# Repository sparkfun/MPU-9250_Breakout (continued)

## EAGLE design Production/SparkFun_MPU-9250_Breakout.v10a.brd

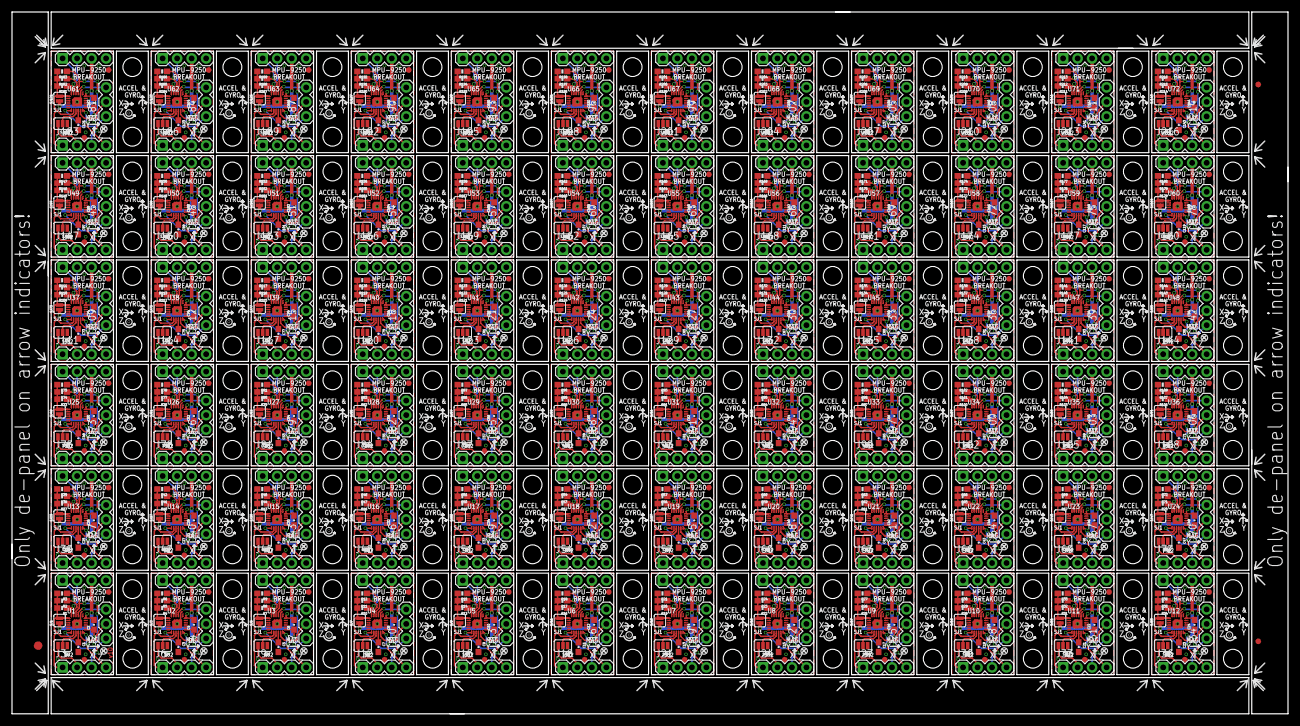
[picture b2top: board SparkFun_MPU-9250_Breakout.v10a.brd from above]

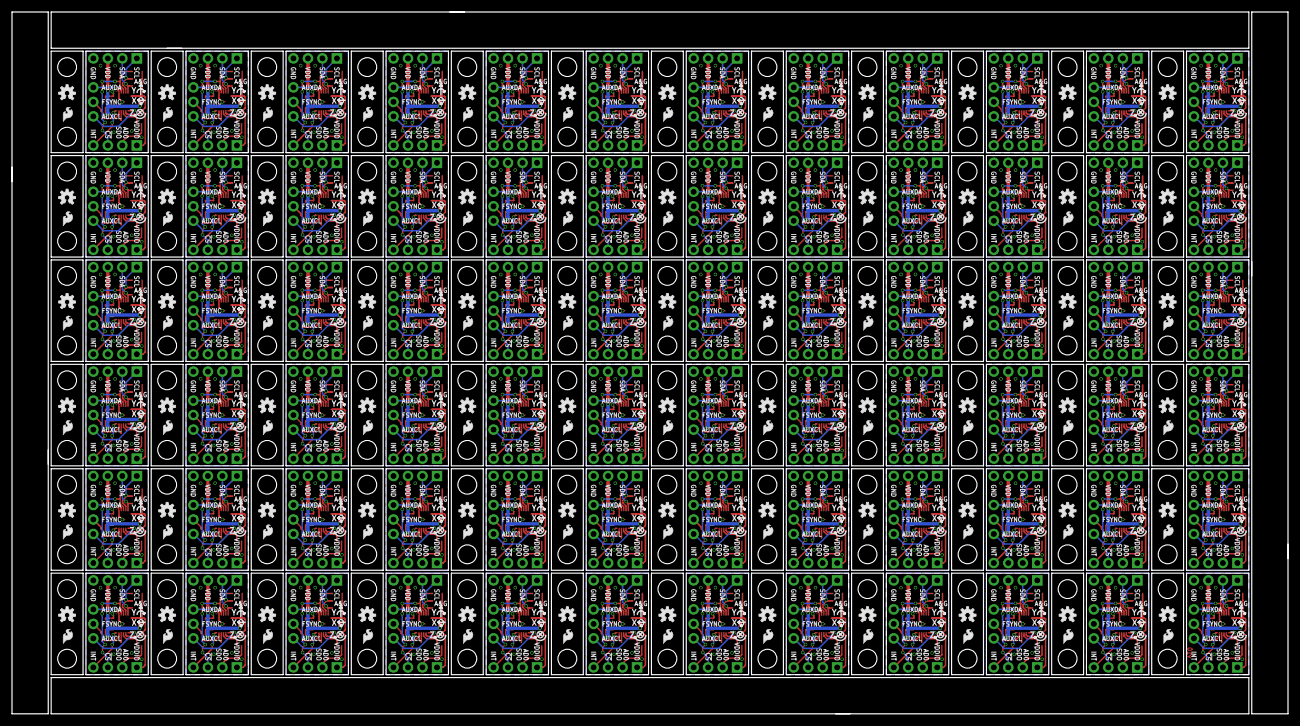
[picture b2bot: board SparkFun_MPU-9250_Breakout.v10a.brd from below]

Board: 2 copper layers, 223.5 x 122.9 mm, 1227 parts (144 on the bottom side), 936 nets.

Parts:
C1, C2, C3, C4, C5, C6, C7, C8, C9, C10, C11, C12, C13, C14, C15, C16, C17, C18, C19, C20, C21, C22, C23, C24, C25, C26, C27, C28, C29, C30, C31, C32, C33, C34, C35, C36, C37, C38, C39, C40, C41, C42, C43, C44, C45, C46, C47, C48, C49, C50, C51, C52, C53, C54, C55, C56, C57, C58, C59, C60, C61, C62, C63, C64, C65, C66, C67, C68, C69, C70, C71, C72, C73, C74, C75, C76, C77, C78, C79, C80, C81, C82, C83, C84, C85, C86, C87, C88, C89, C90, C91, C92, C93, C94, C95, C96, C97, C98, C99, C100, C101, C102, C103, C104, C105, C106, C107, C108, C109, C110, C111, C112, C113, C114, C115, C116, C117, C118, C119, C120, C121, C122, C123, C124, C125, C126, C127, C128, C129, C130, C131, C132, C133, C134, C135, C136, C137, C138, C139, C140, C141, C142, C143, C144: 0.1uF; 0603-CAP
E$1: FIDUCIAL-1.5X3
E$5, E$6: FIDUCIAL-1X2
FID1, FID2, FID3, FID4, FID5, FID6, FID7, FID8, FID9, FID10, FID11, FID12, FID13, FID14, FID15, FID16, FID17, FID18, FID19, FID20, FID21, FID22, FID23, FID24, FID25, FID26, FID27, FID28, FID29, FID30, FID31, FID32, FID33, FID34, FID35, FID36, FID37, FID38, FID39, FID40, FID41, FID42, FID43, FID44, FID45, FID46, FID47, FID48, FID49, FID50, FID51, FID52, FID53, FID54, FID55, FID56, FID57, FID58, FID59, FID60, FID61, FID62, FID63, FID64, FID65, FID66, FID67, FID68, FID69, FID70, FID71, FID72, FID73, FID74, FID75, FID76, FID77, FID78, FID79, FID80, FID81, FID82, FID83, FID84, FID85, FID86, FID87, FID88, FID89, FID90, FID91, FID92, FID93, FID94, FID95, FID96, FID97, FID98, FID99, FID100, FID101, FID102, FID103, FID104, FID105, FID106, FID107, FID108, FID109, FID110, FID111, FID112, FID113, FID114, FID115, FID116, FID117, FID118, FID119, FID120, FID121, FID122, FID123, FID124, FID125, FID126, FID127, FID128, FID129, FID130, FID131, FID132, FID133, FID134, FID135, FID136, FID137, FID138, FID139, FID140, FID141, FID142, FID143, FID144: FIDUCIAL1X2; FIDUCIAL-1X2
J1, J3, J5, J6, J8, J9, J11, J12, J14, J15, J17, J18, J20, J21, J23, J24, J26, J27, J29, J30, J32, J33, J35, J36, J38, J39, J41, J42, J44, J45, J47, J48, J50, J51, J53, J54, J56, J57, J59, J60, J62, J63, J65, J66, J68, J69, J71, J72, J74, J75, J77, J78, J80, J81, J83, J84, J86, J87, J89, J90, J92, J93, J95, J96, J98, J99, J101, J102, J104, J105, J107, J108, J110, J111, J113, J114, J116, J117, J119, J120, J122, J123, J125, J126, J128, J129, J131, J132, J134, J135, J137, J138, J140, J141, J143, J144, J146, J147, J149, J150, J152, J153, J155, J156, J158, J159, J161, J162, J164, J165, J167, J168, J170, J171, J173, J174, J176, J177, J179, J180, J182, J183, J185, J186, J188, J189, J191, J192, J194, J195, J197, J198, J200, J201, J203, J204, J206, J207, J209, J210, J212, J213, J215, J216: 1X04
J2, J4, J7, J10, J13, J16, J19, J22, J25, J28, J31, J34, J37, J40, J43, J46, J49, J52, J55, J58, J61, J64, J67, J70, J73, J76, J79, J82, J85, J88, J91, J94, J97, J100, J103, J106, J109, J112, J115, J118, J121, J124, J127, J130, J133, J136, J139, J142, J145, J148, J151, J154, J157, J160, J163, J166, J169, J172, J175, J178, J181, J184, J187, J190, J193, J196, J199, J202, J205, J208, J211, J214: 1X03
LOGO1, LOGO3, LOGO5, LOGO7, LOGO9, LOGO11, LOGO13, LOGO15, LOGO17, LOGO19, LOGO21, LOGO23, LOGO25, LOGO27, LOGO29, LOGO31, LOGO33, LOGO35, LOGO37, LOGO39, LOGO41, LOGO43, LOGO45, LOGO47, LOGO49, LOGO51, LOGO53, LOGO55, LOGO57, LOGO59, LOGO61, LOGO63, LOGO65, LOGO67, LOGO69, LOGO71, LOGO73, LOGO75, LOGO77, LOGO79, LOGO81, LOGO83, LOGO85, LOGO87, LOGO89, LOGO91, LOGO93, LOGO95, LOGO97, LOGO99, LOGO101, LOGO103, LOGO105, LOGO107, LOGO109, LOGO111, LOGO113, LOGO115, LOGO117, LOGO119, LOGO121, LOGO123, LOGO125, LOGO127, LOGO129, LOGO131, LOGO133, LOGO135, LOGO137, LOGO139, LOGO141, LOGO143: SFE_LOGO_FLAME.1_INCH; SFE_LOGO_FLAME_.1
LOGO2, LOGO4, LOGO6, LOGO8, LOGO10, LOGO12, LOGO14, LOGO16, LOGO18, LOGO20, LOGO22, LOGO24, LOGO26, LOGO28, LOGO30, LOGO32, LOGO34, LOGO36, LOGO38, LOGO40, LOGO42, LOGO44, LOGO46, LOGO48, LOGO50, LOGO52, LOGO54, LOGO56, LOGO58, LOGO60, LOGO62, LOGO64, LOGO66, LOGO68, LOGO70, LOGO72, LOGO74, LOGO76, LOGO78, LOGO80, LOGO82, LOGO84, LOGO86, LOGO88, LOGO90, LOGO92, LOGO94, LOGO96, LOGO98, LOGO100, LOGO102, LOGO104, LOGO106, LOGO108, LOGO110, LOGO112, LOGO114, LOGO116, LOGO118, LOGO120, LOGO122, LOGO124, LOGO126, LOGO128, LOGO130, LOGO132, LOGO134, LOGO136, LOGO138, LOGO140, LOGO142, LOGO144: OSHW-LOGOS; OSHW-LOGO-S
R1, R2, R3, R4, R5, R6, R7, R8, R9, R10, R11, R12, R13, R14, R15, R16, R17, R18, R19, R20, R21, R22, R23, R24, R25, R26, R27, R28, R29, R30, R31, R32, R33, R34, R35, R36, R37, R38, R39, R40, R41, R42, R43, R44, R45, R46, R47, R48, R49, R50, R51, R52, R53, R54, R55, R56, R57, R58, R59, R60, R61, R62, R63, R64, R65, R66, R67, R68, R69, R70, R71, R72, R73, R74, R75, R76, R77, R78, R79, R80, R81, R82, R83, R84, R85, R86, R87, R88, R89, R90, R91, R92, R93, R94, R95, R96, R97, R98, R99, R100, R101, R102, R103, R104, R105, R106, R107, R108, R109, R110, R111, R112, R113, R114, R115, R116, R117, R118, R119, R120, R121, R122, R123, R124, R125, R126, R127, R128, R129, R130, R131, R132, R133, R134, R135, R136, R137, R138, R139, R140, R141, R142, R143, R144, R145, R146, R147, R148, R149, R150, R151, R152, R153, R154, R155, R156, R157, R158, R159, R160, R161, R162, R163, R164, R165, R166, R167, R168, R169, R170, R171, R172, R173, R174, R175, R176, R177, R178, R179, R180, R181, R182, R183, R184, R185, R186, R187, R188, R189, R190, R191, R192, R193, R194, R195, R196, R197, R198, R199, R200, R201, R202, R203, R204, R205, R206, R207, R208, R209, R210, R211, R212, R213, R214, R215, R216: 10K; 0603-RES
SJ1, SJ3, SJ5, SJ7, SJ9, SJ11, SJ13, SJ15, SJ17, SJ19, SJ21, SJ23, SJ25, SJ27, SJ29, SJ31, SJ33, SJ35, SJ37, SJ39, SJ41, SJ43, SJ45, SJ47, SJ49, SJ51, SJ53, SJ55, SJ57, SJ59, SJ61, SJ63, SJ65, SJ67, SJ69, SJ71, SJ73, SJ75, SJ77, SJ79, SJ81, SJ83, SJ85, SJ87, SJ89, SJ91, SJ93, SJ95, SJ97, SJ99, SJ101, SJ103, SJ105, SJ107, SJ109, SJ111, SJ113, SJ115, SJ117, SJ119, SJ121, SJ123, SJ125, SJ127, SJ129, SJ131, SJ133, SJ135, SJ137, SJ139, SJ141, SJ143: JUMPER-PAD-2-NC_BY_PASTEFULL-BOX-SILK; PAD-JUMPER-2-NC_BY_PASTE_YES_SILK_FULL_BOX
SJ2, SJ4, SJ6, SJ8, SJ10, SJ12, SJ14, SJ16, SJ18, SJ20, SJ22, SJ24, SJ26, SJ28, SJ30, SJ32, SJ34, SJ36, SJ38, SJ40, SJ42, SJ44, SJ46, SJ48, SJ50, SJ52, SJ54, SJ56, SJ58, SJ60, SJ62, SJ64, SJ66, SJ68, SJ70, SJ72, SJ74, SJ76, SJ78, SJ80, SJ82, SJ84, SJ86, SJ88, SJ90, SJ92, SJ94, SJ96, SJ98, SJ100, SJ102, SJ104, SJ106, SJ108, SJ110, SJ112, SJ114, SJ116, SJ118, SJ120, SJ122, SJ124, SJ126, SJ128, SJ130, SJ132, SJ134, SJ136, SJ138, SJ140, SJ142, SJ144: JUMPER_PAD-3-1&2_NC_BY_PASTE; PAD-HUMPER-3-1&2_NC_BY_PASTE_YES_SILK_FULL_BOX
STANDOFF1, STANDOFF2, STANDOFF3, STANDOFF4, STANDOFF5, STANDOFF6, STANDOFF7, STANDOFF8, STANDOFF9, STANDOFF10, STANDOFF11, STANDOFF12, STANDOFF13, STANDOFF14, STANDOFF15, STANDOFF16, STANDOFF17, STANDOFF18, STANDOFF19, STANDOFF20, STANDOFF21, STANDOFF22, STANDOFF23, STANDOFF24, STANDOFF25, STANDOFF26, STANDOFF27, STANDOFF28, STANDOFF29, STANDOFF30, STANDOFF31, STANDOFF32, STANDOFF33, STANDOFF34, STANDOFF35, STANDOFF36, STANDOFF37, STANDOFF38, STANDOFF39, STANDOFF40, STANDOFF41, STANDOFF42, STANDOFF43, STANDOFF44, STANDOFF45, STANDOFF46, STANDOFF47, STANDOFF48, STANDOFF49, STANDOFF50, STANDOFF51, STANDOFF52, STANDOFF53, STANDOFF54, STANDOFF55, STANDOFF56, STANDOFF57, STANDOFF58, STANDOFF59, STANDOFF60, STANDOFF61, STANDOFF62, STANDOFF63, STANDOFF64, STANDOFF65, STANDOFF66, STANDOFF67, STANDOFF68, STANDOFF69, STANDOFF70, STANDOFF71, STANDOFF72, STANDOFF73, STANDOFF74, STANDOFF75, STANDOFF76, STANDOFF77, STANDOFF78, STANDOFF79, STANDOFF80, STANDOFF81, STANDOFF82, STANDOFF83, STANDOFF84, STANDOFF85, STANDOFF86, STANDOFF87, STANDOFF88, STANDOFF89, STANDOFF90, STANDOFF91, STANDOFF92, STANDOFF93, STANDOFF94, STANDOFF95, STANDOFF96, STANDOFF97, STANDOFF98, STANDOFF99, STANDOFF100, STANDOFF101, STANDOFF102, STANDOFF103, STANDOFF104, STANDOFF105, STANDOFF106, STANDOFF107, STANDOFF108, STANDOFF109, STANDOFF110, STANDOFF111, STANDOFF112, STANDOFF113, STANDOFF114, STANDOFF115, STANDOFF116, STANDOFF117, STANDOFF118, STANDOFF119, STANDOFF120, STANDOFF121, STANDOFF122, STANDOFF123, STANDOFF124, STANDOFF125, STANDOFF126, STANDOFF127, STANDOFF128, STANDOFF129, STANDOFF130, STANDOFF131, STANDOFF132, STANDOFF133, STANDOFF134, STANDOFF135, STANDOFF136, STANDOFF137, STANDOFF138, STANDOFF139, STANDOFF140, STANDOFF141, STANDOFF142, STANDOFF143, STANDOFF144: STAND-OFF
U1, U2, U3, U4, U5, U6, U7, U8, U9, U10, U11, U12, U13, U14, U15, U16, U17, U18, U19, U20, U21, U22, U23, U24, U25, U26, U27, U28, U29, U30, U31, U32, U33, U34, U35, U36, U37, U38, U39, U40, U41, U42, U43, U44, U45, U46, U47, U48, U49, U50, U51, U52, U53, U54, U55, U56, U57, U58, U59, U60, U61, U62, U63, U64, U65, U66, U67, U68, U69, U70, U71, U72: MPU-9250; QFN24_PAD

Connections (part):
!CS: J3.3, R3.1, U1.22
!CS1: J6.3, R6.1, U2.22
!CS2: J9.3, R9.1, U3.22
!CS3: J12.3, R12.1, U4.22
!CS4: J15.3, R15.1, U5.22
!CS5: J18.3, R18.1, U6.22
!CS6: J21.3, R21.1, U7.22
!CS7: J24.3, R24.1, U8.22
!CS8: J27.3, R27.1, U9.22
!CS9: J30.3, R30.1, U10.22
!CS10: J33.3, R33.1, U11.22
!CS11: J36.3, R36.1, U12.22
!CS12: J39.3, R39.1, U13.22
!CS13: J42.3, R42.1, U14.22
!CS14: J45.3, R45.1, U15.22
!CS15: J48.3, R48.1, U16.22
!CS16: J51.3, R51.1, U17.22
!CS17: J54.3, R54.1, U18.22
!CS18: J57.3, R57.1, U19.22
!CS19: J60.3, R60.1, U20.22
!CS20: J63.3, R63.1, U21.22
!CS21: J66.3, R66.1, U22.22
!CS22: J69.3, R69.1, U23.22
!CS23: J72.3, R72.1, U24.22
!CS24: J75.3, R75.1, U25.22
!CS25: J78.3, R78.1, U26.22
!CS26: J81.3, R81.1, U27.22
!CS27: J84.3, R84.1, U28.22
!CS28: J87.3, R87.1, U29.22
!CS29: J90.3, R90.1, U30.22
!CS30: J93.3, R93.1, U31.22
!CS31: J96.3, R96.1, U32.22
!CS32: J99.3, R99.1, U33.22
!CS33: J102.3, R102.1, U34.22
!CS34: J105.3, R105.1, U35.22
!CS35: J108.3, R108.1, U36.22
!CS36: J111.3, R111.1, U37.22
!CS37: J114.3, R114.1, U38.22
!CS38: J117.3, R117.1, U39.22
!CS39: J120.3, R120.1, U40.22
!CS40: J123.3, R123.1, U41.22
!CS41: J126.3, R126.1, U42.22
!CS42: J129.3, R129.1, U43.22
!CS43: J132.3, R132.1, U44.22
!CS44: J135.3, R135.1, U45.22
!CS45: J138.3, R138.1, U46.22
!CS46: J141.3, R141.1, U47.22
!CS47: J144.3, R144.1, U48.22
!CS48: J147.3, R147.1, U49.22
!CS49: J150.3, R150.1, U50.22
!CS50: J153.3, R153.1, U51.22
!CS51: J156.3, R156.1, U52.22
!CS52: J159.3, R159.1, U53.22
!CS53: J162.3, R162.1, U54.22
!CS54: J165.3, R165.1, U55.22
!CS55: J168.3, R168.1, U56.22
!CS56: J171.3, R171.1, U57.22
!CS57: J174.3, R174.1, U58.22
!CS58: J177.3, R177.1, U59.22
!CS59: J180.3, R180.1, U60.22
!CS60: J183.3, R183.1, U61.22
!CS61: J186.3, R186.1, U62.22
!CS62: J189.3, R189.1, U63.22
!CS63: J192.3, R192.1, U64.22
!CS64: J195.3, R195.1, U65.22
!CS65: J198.3, R198.1, U66.22
!CS66: J201.3, R201.1, U67.22
!CS67: J204.3, R204.1, U68.22
!CS68: J207.3, R207.1, U69.22
!CS69: J210.3, R210.1, U70.22
!CS70: J213.3, R213.1, U71.22
!CS71: J216.3, R216.1, U72.22
AD0/SDO: J3.2, SJ2.3
AD0/SDO1: J6.2, SJ4.3
AD0/SDO2: J9.2, SJ6.3
AD0/SDO3: J12.2, SJ8.3
AD0/SDO4: J15.2, SJ10.3
AD0/SDO5: J18.2, SJ12.3
AD0/SDO6: J21.2, SJ14.3
AD0/SDO7: J24.2, SJ16.3
AD0/SDO8: J27.2, SJ18.3
AD0/SDO9: J30.2, SJ20.3
AD0/SDO10: J33.2, SJ22.3
AD0/SDO11: J36.2, SJ24.3
AD0/SDO12: J39.2, SJ26.3
AD0/SDO13: J42.2, SJ28.3
AD0/SDO14: J45.2, SJ30.3
AD0/SDO15: J48.2, SJ32.3
AD0/SDO16: J51.2, SJ34.3
AD0/SDO17: J54.2, SJ36.3
AD0/SDO18: J57.2, SJ38.3
AD0/SDO19: J60.2, SJ40.3
AD0/SDO20: J63.2, SJ42.3
AD0/SDO21: J66.2, SJ44.3
AD0/SDO22: J69.2, SJ46.3
AD0/SDO23: J72.2, SJ48.3
AD0/SDO24: J75.2, SJ50.3
AD0/SDO25: J78.2, SJ52.3
AD0/SDO26: J81.2, SJ54.3
AD0/SDO27: J84.2, SJ56.3
AD0/SDO28: J87.2, SJ58.3
AD0/SDO29: J90.2, SJ60.3
AD0/SDO30: J93.2, SJ62.3
AD0/SDO31: J96.2, SJ64.3
AD0/SDO32: J99.2, SJ66.3
AD0/SDO33: J102.2, SJ68.3
AD0/SDO34: J105.2, SJ70.3
AD0/SDO35: J108.2, SJ72.3
AD0/SDO36: J111.2, SJ74.3
AD0/SDO37: J114.2, SJ76.3
AD0/SDO38: J117.2, SJ78.3
AD0/SDO39: J120.2, SJ80.3
AD0/SDO40: J123.2, SJ82.3
AD0/SDO41: J126.2, SJ84.3
AD0/SDO42: J129.2, SJ86.3
AD0/SDO43: J132.2, SJ88.3
AD0/SDO44: J135.2, SJ90.3
AD0/SDO45: J138.2, SJ92.3
AD0/SDO46: J141.2, SJ94.3
AD0/SDO47: J144.2, SJ96.3
AD0/SDO48: J147.2, SJ98.3
AD0/SDO49: J150.2, SJ100.3
AD0/SDO50: J153.2, SJ102.3
AD0/SDO51: J156.2, SJ104.3
AD0/SDO52: J159.2, SJ106.3
AD0/SDO53: J162.2, SJ108.3
AD0/SDO54: J165.2, SJ110.3
AD0/SDO55: J168.2, SJ112.3
AD0/SDO56: J171.2, SJ114.3
AD0/SDO57: J174.2, SJ116.3
AD0/SDO58: J177.2, SJ118.3
AD0/SDO59: J180.2, SJ120.3
AD0/SDO60: J183.2, SJ122.3
AD0/SDO61: J186.2, SJ124.3
AD0/SDO62: J189.2, SJ126.3
AD0/SDO63: J192.2, SJ128.3
AD0/SDO64: J195.2, SJ130.3
AD0/SDO65: J198.2, SJ132.3
AD0/SDO66: J201.2, SJ134.3
AD0/SDO67: J204.2, SJ136.3
AD0/SDO68: J207.2, SJ138.3
AD0/SDO69: J210.2, SJ140.3
AD0/SDO70: J213.2, SJ142.3
AD0/SDO71: J216.2, SJ144.3
ADSD_STUB: SJ2.2, U1.9
ADSD_STUB1: SJ4.2, U2.9
ADSD_STUB2: SJ6.2, U3.9
ADSD_STUB3: SJ8.2, U4.9
ADSD_STUB4: SJ10.2, U5.9
ADSD_STUB5: SJ12.2, U6.9
ADSD_STUB6: SJ14.2, U7.9
ADSD_STUB7: SJ16.2, U8.9
ADSD_STUB8: SJ18.2, U9.9
ADSD_STUB9: SJ20.2, U10.9
ADSD_STUB10: SJ22.2, U11.9
ADSD_STUB11: SJ24.2, U12.9
ADSD_STUB12: SJ26.2, U13.9
ADSD_STUB13: SJ28.2, U14.9
ADSD_STUB14: SJ30.2, U15.9
ADSD_STUB15: SJ32.2, U16.9
ADSD_STUB16: SJ34.2, U17.9
ADSD_STUB17: SJ36.2, U18.9
ADSD_STUB18: SJ38.2, U19.9
ADSD_STUB19: SJ40.2, U20.9
ADSD_STUB20: SJ42.2, U21.9
ADSD_STUB21: SJ44.2, U22.9
ADSD_STUB22: SJ46.2, U23.9
ADSD_STUB23: SJ48.2, U24.9
ADSD_STUB24: SJ50.2, U25.9
ADSD_STUB25: SJ52.2, U26.9
ADSD_STUB26: SJ54.2, U27.9
ADSD_STUB27: SJ56.2, U28.9
ADSD_STUB28: SJ58.2, U29.9
ADSD_STUB29: SJ60.2, U30.9
ADSD_STUB30: SJ62.2, U31.9
ADSD_STUB31: SJ64.2, U32.9
ADSD_STUB32: SJ66.2, U33.9
ADSD_STUB33: SJ68.2, U34.9
ADSD_STUB34: SJ70.2, U35.9
ADSD_STUB35: SJ72.2, U36.9
ADSD_STUB36: SJ74.2, U37.9
ADSD_STUB37: SJ76.2, U38.9
ADSD_STUB38: SJ78.2, U39.9
ADSD_STUB39: SJ80.2, U40.9
ADSD_STUB40: SJ82.2, U41.9
ADSD_STUB41: SJ84.2, U42.9
ADSD_STUB42: SJ86.2, U43.9
ADSD_STUB43: SJ88.2, U44.9
ADSD_STUB44: SJ90.2, U45.9
ADSD_STUB45: SJ92.2, U46.9
ADSD_STUB46: SJ94.2, U47.9
ADSD_STUB47: SJ96.2, U48.9
ADSD_STUB48: SJ98.2, U49.9
ADSD_STUB49: SJ100.2, U50.9
ADSD_STUB50: SJ102.2, U51.9
ADSD_STUB51: SJ104.2, U52.9
ADSD_STUB52: SJ106.2, U53.9
ADSD_STUB53: SJ108.2, U54.9
ADSD_STUB54: SJ110.2, U55.9
ADSD_STUB55: SJ112.2, U56.9
ADSD_STUB56: SJ114.2, U57.9
ADSD_STUB57: SJ116.2, U58.9
ADSD_STUB58: SJ118.2, U59.9
ADSD_STUB59: SJ120.2, U60.9
ADSD_STUB60: SJ122.2, U61.9
ADSD_STUB61: SJ124.2, U62.9
ADSD_STUB62: SJ126.2, U63.9
ADSD_STUB63: SJ128.2, U64.9
ADSD_STUB64: SJ130.2, U65.9
ADSD_STUB65: SJ132.2, U66.9
ADSD_STUB66: SJ134.2, U67.9
ADSD_STUB67: SJ136.2, U68.9
ADSD_STUB68: SJ138.2, U69.9
ADSD_STUB69: SJ140.2, U70.9
ADSD_STUB70: SJ142.2, U71.9
ADSD_STUB71: SJ144.2, U72.9
AUX_CL: J2.1, U1.7
AUX_CL1: J4.1, U2.7
AUX_CL2: J7.1, U3.7
AUX_CL3: J10.1, U4.7
AUX_CL4: J13.1, U5.7
AUX_CL5: J16.1, U6.7
AUX_CL6: J19.1, U7.7
AUX_CL7: J22.1, U8.7
AUX_CL8: J25.1, U9.7
AUX_CL9: J28.1, U10.7
AUX_CL10: J31.1, U11.7
AUX_CL11: J34.1, U12.7
AUX_CL12: J37.1, U13.7
AUX_CL13: J40.1, U14.7
AUX_CL14: J43.1, U15.7
AUX_CL15: J46.1, U16.7
AUX_CL16: J49.1, U17.7
AUX_CL17: J52.1, U18.7
AUX_CL18: J55.1, U19.7
AUX_CL19: J58.1, U20.7
AUX_CL20: J61.1, U21.7
AUX_CL21: J64.1, U22.7
AUX_CL22: J67.1, U23.7
AUX_CL23: J70.1, U24.7
AUX_CL24: J73.1, U25.7
AUX_CL25: J76.1, U26.7
AUX_CL26: J79.1, U27.7
AUX_CL27: J82.1, U28.7
AUX_CL28: J85.1, U29.7
AUX_CL29: J88.1, U30.7
AUX_CL30: J91.1, U31.7
AUX_CL31: J94.1, U32.7
AUX_CL32: J97.1, U33.7
AUX_CL33: J100.1, U34.7
AUX_CL34: J103.1, U35.7
AUX_CL35: J106.1, U36.7
AUX_CL36: J109.1, U37.7
AUX_CL37: J112.1, U38.7
AUX_CL38: J115.1, U39.7
AUX_CL39: J118.1, U40.7
AUX_CL40: J121.1, U41.7
AUX_CL41: J124.1, U42.7
AUX_CL42: J127.1, U43.7
AUX_CL43: J130.1, U44.7
AUX_CL44: J133.1, U45.7
AUX_CL45: J136.1, U46.7
AUX_CL46: J139.1, U47.7
AUX_CL47: J142.1, U48.7
AUX_CL48: J145.1, U49.7
AUX_CL49: J148.1, U50.7
AUX_CL50: J151.1, U51.7
AUX_CL51: J154.1, U52.7
AUX_CL52: J157.1, U53.7
AUX_CL53: J160.1, U54.7
AUX_CL54: J163.1, U55.7
AUX_CL55: J166.1, U56.7
AUX_CL56: J169.1, U57.7
AUX_CL57: J172.1, U58.7
AUX_CL58: J175.1, U59.7
AUX_CL59: J178.1, U60.7
AUX_CL60: J181.1, U61.7
AUX_CL61: J184.1, U62.7
AUX_CL62: J187.1, U63.7
AUX_CL63: J190.1, U64.7
AUX_CL64: J193.1, U65.7
AUX_CL65: J196.1, U66.7
AUX_CL66: J199.1, U67.7
AUX_CL67: J202.1, U68.7
AUX_CL68: J205.1, U69.7
AUX_CL69: J208.1, U70.7
AUX_CL70: J211.1, U71.7
AUX_CL71: J214.1, U72.7
AUX_DA: J2.3, U1.21
AUX_DA1: J4.3, U2.21
AUX_DA2: J7.3, U3.21
AUX_DA3: J10.3, U4.21
AUX_DA4: J13.3, U5.21
AUX_DA5: J16.3, U6.21
AUX_DA6: J19.3, U7.21
AUX_DA7: J22.3, U8.21
AUX_DA8: J25.3, U9.21
AUX_DA9: J28.3, U10.21
AUX_DA10: J31.3, U11.21
AUX_DA11: J34.3, U12.21
AUX_DA12: J37.3, U13.21
AUX_DA13: J40.3, U14.21
AUX_DA14: J43.3, U15.21
AUX_DA15: J46.3, U16.21
AUX_DA16: J49.3, U17.21
AUX_DA17: J52.3, U18.21
AUX_DA18: J55.3, U19.21
AUX_DA19: J58.3, U20.21
AUX_DA20: J61.3, U21.21
AUX_DA21: J64.3, U22.21
AUX_DA22: J67.3, U23.21
AUX_DA23: J70.3, U24.21
AUX_DA24: J73.3, U25.21
AUX_DA25: J76.3, U26.21
AUX_DA26: J79.3, U27.21
AUX_DA27: J82.3, U28.21
AUX_DA28: J85.3, U29.21
AUX_DA29: J88.3, U30.21
AUX_DA30: J91.3, U31.21
AUX_DA31: J94.3, U32.21
AUX_DA32: J97.3, U33.21
AUX_DA33: J100.3, U34.21
AUX_DA34: J103.3, U35.21
AUX_DA35: J106.3, U36.21
AUX_DA36: J109.3, U37.21
AUX_DA37: J112.3, U38.21
AUX_DA38: J115.3, U39.21
AUX_DA39: J118.3, U40.21
AUX_DA40: J121.3, U41.21
AUX_DA41: J124.3, U42.21
AUX_DA42: J127.3, U43.21
AUX_DA43: J130.3, U44.21
AUX_DA44: J133.3, U45.21
AUX_DA45: J136.3, U46.21
AUX_DA46: J139.3, U47.21
AUX_DA47: J142.3, U48.21
AUX_DA48: J145.3, U49.21
AUX_DA49: J148.3, U50.21
AUX_DA50: J151.3, U51.21
AUX_DA51: J154.3, U52.21
AUX_DA52: J157.3, U53.21
AUX_DA53: J160.3, U54.21
AUX_DA54: J163.3, U55.21
AUX_DA55: J166.3, U56.21
AUX_DA56: J169.3, U57.21
AUX_DA57: J172.3, U58.21
AUX_DA58: J175.3, U59.21
AUX_DA59: J178.3, U60.21
AUX_DA60: J181.3, U61.21
AUX_DA61: J184.3, U62.21
AUX_DA62: J187.3, U63.21
AUX_DA63: J190.3, U64.21
AUX_DA64: J193.3, U65.21
AUX_DA65: J196.3, U66.21
AUX_DA66: J199.3, U67.21
AUX_DA67: J202.3, U68.21
AUX_DA68: J205.3, U69.21
AUX_DA69: J208.3, U70.21
AUX_DA70: J211.3, U71.21
AUX_DA71: J214.3, U72.21
FSYNC: J2.2, U1.11
FSYNC1: J4.2, U2.11
FSYNC2: J7.2, U3.11
FSYNC3: J10.2, U4.11
FSYNC4: J13.2, U5.11
FSYNC5: J16.2, U6.11
FSYNC6: J19.2, U7.11
FSYNC7: J22.2, U8.11
FSYNC8: J25.2, U9.11
FSYNC9: J28.2, U10.11
FSYNC10: J31.2, U11.11
FSYNC11: J34.2, U12.11
FSYNC12: J37.2, U13.11
FSYNC13: J40.2, U14.11
FSYNC14: J43.2, U15.11
FSYNC15: J46.2, U16.11
FSYNC16: J49.2, U17.11
FSYNC17: J52.2, U18.11
FSYNC18: J55.2, U19.11
FSYNC19: J58.2, U20.11
FSYNC20: J61.2, U21.11
FSYNC21: J64.2, U22.11
FSYNC22: J67.2, U23.11
FSYNC23: J70.2, U24.11
FSYNC24: J73.2, U25.11
FSYNC25: J76.2, U26.11
FSYNC26: J79.2, U27.11
FSYNC27: J82.2, U28.11
FSYNC28: J85.2, U29.11
FSYNC29: J88.2, U30.11
FSYNC30: J91.2, U31.11
FSYNC31: J94.2, U32.11
FSYNC32: J97.2, U33.11
FSYNC33: J100.2, U34.11
FSYNC34: J103.2, U35.11
FSYNC35: J106.2, U36.11
FSYNC36: J109.2, U37.11
FSYNC37: J112.2, U38.11
FSYNC38: J115.2, U39.11
FSYNC39: J118.2, U40.11
FSYNC40: J121.2, U41.11
FSYNC41: J124.2, U42.11
FSYNC42: J127.2, U43.11
FSYNC43: J130.2, U44.11
FSYNC44: J133.2, U45.11
FSYNC45: J136.2, U46.11
FSYNC46: J139.2, U47.11
FSYNC47: J142.2, U48.11
FSYNC48: J145.2, U49.11
FSYNC49: J148.2, U50.11
FSYNC50: J151.2, U51.11
FSYNC51: J154.2, U52.11
FSYNC52: J157.2, U53.11
FSYNC53: J160.2, U54.11
FSYNC54: J163.2, U55.11
FSYNC55: J166.2, U56.11
FSYNC56: J169.2, U57.11
FSYNC57: J172.2, U58.11
FSYNC58: J175.2, U59.11
FSYNC59: J178.2, U60.11
FSYNC60: J181.2, U61.11
FSYNC61: J184.2, U62.11
FSYNC62: J187.2, U63.11
FSYNC63: J190.2, U64.11
FSYNC64: J193.2, U65.11
FSYNC65: J196.2, U66.11
FSYNC66: J199.2, U67.11
FSYNC67: J202.2, U68.11
FSYNC68: J205.2, U69.11
FSYNC69: J208.2, U70.11
FSYNC70: J211.2, U71.11
FSYNC71: J214.2, U72.11
GND: C1.2, C2.2, J1.4, SJ2.1, U1.18, U1.20, U1.CENTER
GND1: C3.2, C4.2, J5.4, SJ4.1, U2.18, U2.20, U2.CENTER
GND2: C5.2, C6.2, J8.4, SJ6.1, U3.18, U3.20, U3.CENTER
GND3: C7.2, C8.2, J11.4, SJ8.1, U4.18, U4.20, U4.CENTER
GND4: C9.2, C10.2, J14.4, SJ10.1, U5.18, U5.20, U5.CENTER
GND5: C11.2, C12.2, J17.4, SJ12.1, U6.18, U6.20, U6.CENTER
GND6: C13.2, C14.2, J20.4, SJ14.1, U7.18, U7.20, U7.CENTER
GND7: C15.2, C16.2, J23.4, SJ16.1, U8.18, U8.20, U8.CENTER
GND8: C17.2, C18.2, J26.4, SJ18.1, U9.18, U9.20, U9.CENTER
GND9: C19.2, C20.2, J29.4, SJ20.1, U10.18, U10.20, U10.CENTER
GND10: C21.2, C22.2, J32.4, SJ22.1, U11.18, U11.20, U11.CENTER
GND11: C23.2, C24.2, J35.4, SJ24.1, U12.18, U12.20, U12.CENTER
GND12: C25.2, C26.2, J38.4, SJ26.1, U13.18, U13.20, U13.CENTER
GND13: C27.2, C28.2, J41.4, SJ28.1, U14.18, U14.20, U14.CENTER
GND14: C29.2, C30.2, J44.4, SJ30.1, U15.18, U15.20, U15.CENTER
GND15: C31.2, C32.2, J47.4, SJ32.1, U16.18, U16.20, U16.CENTER
GND16: C33.2, C34.2, J50.4, SJ34.1, U17.18, U17.20, U17.CENTER
GND17: C35.2, C36.2, J53.4, SJ36.1, U18.18, U18.20, U18.CENTER
GND18: C37.2, C38.2, J56.4, SJ38.1, U19.18, U19.20, U19.CENTER
GND19: C39.2, C40.2, J59.4, SJ40.1, U20.18, U20.20, U20.CENTER
GND20: C41.2, C42.2, J62.4, SJ42.1, U21.18, U21.20, U21.CENTER
GND21: C43.2, C44.2, J65.4, SJ44.1, U22.18, U22.20, U22.CENTER
GND22: C45.2, C46.2, J68.4, SJ46.1, U23.18, U23.20, U23.CENTER
GND23: C47.2, C48.2, J71.4, SJ48.1, U24.18, U24.20, U24.CENTER
GND24: C49.2, C50.2, J74.4, SJ50.1, U25.18, U25.20, U25.CENTER
GND25: C51.2, C52.2, J77.4, SJ52.1, U26.18, U26.20, U26.CENTER
GND26: C53.2, C54.2, J80.4, SJ54.1, U27.18, U27.20, U27.CENTER
GND27: C55.2, C56.2, J83.4, SJ56.1, U28.18, U28.20, U28.CENTER
GND28: C57.2, C58.2, J86.4, SJ58.1, U29.18, U29.20, U29.CENTER
GND29: C59.2, C60.2, J89.4, SJ60.1, U30.18, U30.20, U30.CENTER
GND30: C61.2, C62.2, J92.4, SJ62.1, U31.18, U31.20, U31.CENTER
GND31: C63.2, C64.2, J95.4, SJ64.1, U32.18, U32.20, U32.CENTER
GND32: C65.2, C66.2, J98.4, SJ66.1, U33.18, U33.20, U33.CENTER
GND33: C67.2, C68.2, J101.4, SJ68.1, U34.18, U34.20, U34.CENTER
GND34: C69.2, C70.2, J104.4, SJ70.1, U35.18, U35.20, U35.CENTER
GND35: C71.2, C72.2, J107.4, SJ72.1, U36.18, U36.20, U36.CENTER
GND36: C73.2, C74.2, J110.4, SJ74.1, U37.18, U37.20, U37.CENTER
GND37: C75.2, C76.2, J113.4, SJ76.1, U38.18, U38.20, U38.CENTER
GND38: C77.2, C78.2, J116.4, SJ78.1, U39.18, U39.20, U39.CENTER
GND39: C79.2, C80.2, J119.4, SJ80.1, U40.18, U40.20, U40.CENTER
GND40: C81.2, C82.2, J122.4, SJ82.1, U41.18, U41.20, U41.CENTER
GND41: C83.2, C84.2, J125.4, SJ84.1, U42.18, U42.20, U42.CENTER
GND42: C85.2, C86.2, J128.4, SJ86.1, U43.18, U43.20, U43.CENTER
GND43: C87.2, C88.2, J131.4, SJ88.1, U44.18, U44.20, U44.CENTER
GND44: C89.2, C90.2, J134.4, SJ90.1, U45.18, U45.20, U45.CENTER
GND45: C91.2, C92.2, J137.4, SJ92.1, U46.18, U46.20, U46.CENTER
GND46: C93.2, C94.2, J140.4, SJ94.1, U47.18, U47.20, U47.CENTER
GND47: C95.2, C96.2, J143.4, SJ96.1, U48.18, U48.20, U48.CENTER
GND48: C97.2, C98.2, J146.4, SJ98.1, U49.18, U49.20, U49.CENTER
GND49: C99.2, C100.2, J149.4, SJ100.1, U50.18, U50.20, U50.CENTER
GND50: C101.2, C102.2, J152.4, SJ102.1, U51.18, U51.20, U51.CENTER
GND51: C103.2, C104.2, J155.4, SJ104.1, U52.18, U52.20, U52.CENTER
GND52: C105.2, C106.2, J158.4, SJ106.1, U53.18, U53.20, U53.CENTER
GND53: C107.2, C108.2, J161.4, SJ108.1, U54.18, U54.20, U54.CENTER
GND54: C109.2, C110.2, J164.4, SJ110.1, U55.18, U55.20, U55.CENTER
GND55: C111.2, C112.2, J167.4, SJ112.1, U56.18, U56.20, U56.CENTER
GND56: C113.2, C114.2, J170.4, SJ114.1, U57.18, U57.20, U57.CENTER
GND57: C115.2, C116.2, J173.4, SJ116.1, U58.18, U58.20, U58.CENTER
GND58: C117.2, C118.2, J176.4, SJ118.1, U59.18, U59.20, U59.CENTER
GND59: C119.2, C120.2, J179.4, SJ120.1, U60.18, U60.20, U60.CENTER
GND60: C121.2, C122.2, J182.4, SJ122.1, U61.18, U61.20, U61.CENTER
GND61: C123.2, C124.2, J185.4, SJ124.1, U62.18, U62.20, U62.CENTER
GND62: C125.2, C126.2, J188.4, SJ126.1, U63.18, U63.20, U63.CENTER
GND63: C127.2, C128.2, J191.4, SJ128.1, U64.18, U64.20, U64.CENTER
GND64: C129.2, C130.2, J194.4, SJ130.1, U65.18, U65.20, U65.CENTER
GND65: C131.2, C132.2, J197.4, SJ132.1, U66.18, U66.20, U66.CENTER
GND66: C133.2, C134.2, J200.4, SJ134.1, U67.18, U67.20, U67.CENTER
GND67: C135.2, C136.2, J203.4, SJ136.1, U68.18, U68.20, U68.CENTER
GND68: C137.2, C138.2, J206.4, SJ138.1, U69.18, U69.20, U69.CENTER
GND69: C139.2, C140.2, J209.4, SJ140.1, U70.18, U70.20, U70.CENTER
GND70: C141.2, C142.2, J212.4, SJ142.1, U71.18, U71.20, U71.CENTER
GND71: C143.2, C144.2, J215.4, SJ144.1, U72.18, U72.20, U72.CENTER
INT: J3.4, U1.12
INT1: J6.4, U2.12
INT2: J9.4, U3.12
INT3: J12.4, U4.12
INT4: J15.4, U5.12
INT5: J18.4, U6.12
INT6: J21.4, U7.12
INT7: J24.4, U8.12
INT8: J27.4, U9.12
INT9: J30.4, U10.12
INT10: J33.4, U11.12
INT11: J36.4, U12.12
INT12: J39.4, U13.12
INT13: J42.4, U14.12
INT14: J45.4, U15.12
INT15: J48.4, U16.12
INT16: J51.4, U17.12
INT17: J54.4, U18.12
INT18: J57.4, U19.12
INT19: J60.4, U20.12
INT20: J63.4, U21.12
INT21: J66.4, U22.12
INT22: J69.4, U23.12
INT23: J72.4, U24.12
INT24: J75.4, U25.12
INT25: J78.4, U26.12
INT26: J81.4, U27.12
INT27: J84.4, U28.12
INT28: J87.4, U29.12
INT29: J90.4, U30.12
INT30: J93.4, U31.12
INT31: J96.4, U32.12
INT32: J99.4, U33.12
INT33: J102.4, U34.12
INT34: J105.4, U35.12
INT35: J108.4, U36.12
INT36: J111.4, U37.12
INT37: J114.4, U38.12
INT38: J117.4, U39.12
INT39: J120.4, U40.12
INT40: J123.4, U41.12
INT41: J126.4, U42.12
INT42: J129.4, U43.12
INT43: J132.4, U44.12
INT44: J135.4, U45.12
INT45: J138.4, U46.12
INT46: J141.4, U47.12
INT47: J144.4, U48.12
INT48: J147.4, U49.12
INT49: J150.4, U50.12
INT50: J153.4, U51.12
INT51: J156.4, U52.12
INT52: J159.4, U53.12
INT53: J162.4, U54.12
INT54: J165.4, U55.12
INT55: J168.4, U56.12
INT56: J171.4, U57.12
INT57: J174.4, U58.12
INT58: J177.4, U59.12
INT59: J180.4, U60.12
INT60: J183.4, U61.12
INT61: J186.4, U62.12
INT62: J189.4, U63.12
INT63: J192.4, U64.12
INT64: J195.4, U65.12
INT65: J198.4, U66.12
INT66: J201.4, U67.12
INT67: J204.4, U68.12
INT68: J207.4, U69.12
INT69: J210.4, U70.12
INT70: J213.4, U71.12
INT71: J216.4, U72.12
REGOUT: C1.1, U1.10
REGOUT1: C3.1, U2.10
REGOUT2: C5.1, U3.10
REGOUT3: C7.1, U4.10
REGOUT4: C9.1, U5.10
REGOUT5: C11.1, U6.10
REGOUT6: C13.1, U7.10
REGOUT7: C15.1, U8.10
REGOUT8: C17.1, U9.10
REGOUT9: C19.1, U10.10
REGOUT10: C21.1, U11.10
REGOUT11: C23.1, U12.10
REGOUT12: C25.1, U13.10
REGOUT13: C27.1, U14.10
REGOUT14: C29.1, U15.10
REGOUT15: C31.1, U16.10
REGOUT16: C33.1, U17.10
REGOUT17: C35.1, U18.10
REGOUT18: C37.1, U19.10
REGOUT19: C39.1, U20.10
REGOUT20: C41.1, U21.10
REGOUT21: C43.1, U22.10
REGOUT22: C45.1, U23.10
REGOUT23: C47.1, U24.10
REGOUT24: C49.1, U25.10
REGOUT25: C51.1, U26.10
REGOUT26: C53.1, U27.10
REGOUT27: C55.1, U28.10
REGOUT28: C57.1, U29.10
REGOUT29: C59.1, U30.10
REGOUT30: C61.1, U31.10
REGOUT31: C63.1, U32.10
REGOUT32: C65.1, U33.10
REGOUT33: C67.1, U34.10
REGOUT34: C69.1, U35.10
REGOUT35: C71.1, U36.10
REGOUT36: C73.1, U37.10
REGOUT37: C75.1, U38.10
REGOUT38: C77.1, U39.10
REGOUT39: C79.1, U40.10
REGOUT40: C81.1, U41.10
REGOUT41: C83.1, U42.10
REGOUT42: C85.1, U43.10
REGOUT43: C87.1, U44.10
REGOUT44: C89.1, U45.10
REGOUT45: C91.1, U46.10
REGOUT46: C93.1, U47.10
REGOUT47: C95.1, U48.10
REGOUT48: C97.1, U49.10
REGOUT49: C99.1, U50.10
REGOUT50: C101.1, U51.10
REGOUT51: C103.1, U52.10
REGOUT52: C105.1, U53.10
REGOUT53: C107.1, U54.10
REGOUT54: C109.1, U55.10
REGOUT55: C111.1, U56.10
REGOUT56: C113.1, U57.10
REGOUT57: C115.1, U58.10
REGOUT58: C117.1, U59.10
REGOUT59: C119.1, U60.10
REGOUT60: C121.1, U61.10
REGOUT61: C123.1, U62.10
REGOUT62: C125.1, U63.10
REGOUT63: C127.1, U64.10
REGOUT64: C129.1, U65.10
REGOUT65: C131.1, U66.10
REGOUT66: C133.1, U67.10
REGOUT67: C135.1, U68.10
REGOUT68: C137.1, U69.10
REGOUT69: C139.1, U70.10
REGOUT70: C141.1, U71.10
REGOUT71: C143.1, U72.10
SCL/SCLK: J1.1, R2.1, U1.23
SCL/SCLK1: J5.1, R5.1, U2.23
SCL/SCLK2: J8.1, R8.1, U3.23
SCL/SCLK3: J11.1, R11.1, U4.23
SCL/SCLK4: J14.1, R14.1, U5.23
SCL/SCLK5: J17.1, R17.1, U6.23
SCL/SCLK6: J20.1, R20.1, U7.23
SCL/SCLK7: J23.1, R23.1, U8.23
SCL/SCLK8: J26.1, R26.1, U9.23
SCL/SCLK9: J29.1, R29.1, U10.23
SCL/SCLK10: J32.1, R32.1, U11.23
SCL/SCLK11: J35.1, R35.1, U12.23
SCL/SCLK12: J38.1, R38.1, U13.23
SCL/SCLK13: J41.1, R41.1, U14.23
SCL/SCLK14: J44.1, R44.1, U15.23
SCL/SCLK15: J47.1, R47.1, U16.23
SCL/SCLK16: J50.1, R50.1, U17.23
SCL/SCLK17: J53.1, R53.1, U18.23
SCL/SCLK18: J56.1, R56.1, U19.23
SCL/SCLK19: J59.1, R59.1, U20.23
SCL/SCLK20: J62.1, R62.1, U21.23
SCL/SCLK21: J65.1, R65.1, U22.23
SCL/SCLK22: J68.1, R68.1, U23.23
SCL/SCLK23: J71.1, R71.1, U24.23
SCL/SCLK24: J74.1, R74.1, U25.23
SCL/SCLK25: J77.1, R77.1, U26.23
SCL/SCLK26: J80.1, R80.1, U27.23
SCL/SCLK27: J83.1, R83.1, U28.23
SCL/SCLK28: J86.1, R86.1, U29.23
SCL/SCLK29: J89.1, R89.1, U30.23
SCL/SCLK30: J92.1, R92.1, U31.23
SCL/SCLK31: J95.1, R95.1, U32.23
SCL/SCLK32: J98.1, R98.1, U33.23
SCL/SCLK33: J101.1, R101.1, U34.23
SCL/SCLK34: J104.1, R104.1, U35.23
SCL/SCLK35: J107.1, R107.1, U36.23
SCL/SCLK36: J110.1, R110.1, U37.23
SCL/SCLK37: J113.1, R113.1, U38.23
SCL/SCLK38: J116.1, R116.1, U39.23
SCL/SCLK39: J119.1, R119.1, U40.23
SCL/SCLK40: J122.1, R122.1, U41.23
SCL/SCLK41: J125.1, R125.1, U42.23
SCL/SCLK42: J128.1, R128.1, U43.23
SCL/SCLK43: J131.1, R131.1, U44.23
SCL/SCLK44: J134.1, R134.1, U45.23
SCL/SCLK45: J137.1, R137.1, U46.23
SCL/SCLK46: J140.1, R140.1, U47.23
SCL/SCLK47: J143.1, R143.1, U48.23
SCL/SCLK48: J146.1, R146.1, U49.23
SCL/SCLK49: J149.1, R149.1, U50.23
SCL/SCLK50: J152.1, R152.1, U51.23
SCL/SCLK51: J155.1, R155.1, U52.23
SCL/SCLK52: J158.1, R158.1, U53.23
SCL/SCLK53: J161.1, R161.1, U54.23
SCL/SCLK54: J164.1, R164.1, U55.23
SCL/SCLK55: J167.1, R167.1, U56.23
SCL/SCLK56: J170.1, R170.1, U57.23
SCL/SCLK57: J173.1, R173.1, U58.23
SCL/SCLK58: J176.1, R176.1, U59.23
SCL/SCLK59: J179.1, R179.1, U60.23
SCL/SCLK60: J182.1, R182.1, U61.23
SCL/SCLK61: J185.1, R185.1, U62.23
SCL/SCLK62: J188.1, R188.1, U63.23
SCL/SCLK63: J191.1, R191.1, U64.23
SCL/SCLK64: J194.1, R194.1, U65.23
SCL/SCLK65: J197.1, R197.1, U66.23
SCL/SCLK66: J200.1, R200.1, U67.23
SCL/SCLK67: J203.1, R203.1, U68.23
SCL/SCLK68: J206.1, R206.1, U69.23
SCL/SCLK69: J209.1, R209.1, U70.23
SCL/SCLK70: J212.1, R212.1, U71.23
SCL/SCLK71: J215.1, R215.1, U72.23
SDA/SDI: J1.2, R1.1, U1.24
SDA/SDI1: J5.2, R4.1, U2.24
SDA/SDI2: J8.2, R7.1, U3.24
SDA/SDI3: J11.2, R10.1, U4.24
SDA/SDI4: J14.2, R13.1, U5.24
SDA/SDI5: J17.2, R16.1, U6.24
SDA/SDI6: J20.2, R19.1, U7.24
SDA/SDI7: J23.2, R22.1, U8.24
SDA/SDI8: J26.2, R25.1, U9.24
SDA/SDI9: J29.2, R28.1, U10.24
SDA/SDI10: J32.2, R31.1, U11.24
SDA/SDI11: J35.2, R34.1, U12.24
SDA/SDI12: J38.2, R37.1, U13.24
SDA/SDI13: J41.2, R40.1, U14.24
SDA/SDI14: J44.2, R43.1, U15.24
SDA/SDI15: J47.2, R46.1, U16.24
SDA/SDI16: J50.2, R49.1, U17.24
SDA/SDI17: J53.2, R52.1, U18.24
SDA/SDI18: J56.2, R55.1, U19.24
SDA/SDI19: J59.2, R58.1, U20.24
SDA/SDI20: J62.2, R61.1, U21.24
SDA/SDI21: J65.2, R64.1, U22.24
SDA/SDI22: J68.2, R67.1, U23.24
SDA/SDI23: J71.2, R70.1, U24.24
SDA/SDI24: J74.2, R73.1, U25.24
SDA/SDI25: J77.2, R76.1, U26.24
SDA/SDI26: J80.2, R79.1, U27.24
SDA/SDI27: J83.2, R82.1, U28.24
SDA/SDI28: J86.2, R85.1, U29.24
SDA/SDI29: J89.2, R88.1, U30.24
SDA/SDI30: J92.2, R91.1, U31.24
SDA/SDI31: J95.2, R94.1, U32.24
SDA/SDI32: J98.2, R97.1, U33.24
SDA/SDI33: J101.2, R100.1, U34.24
SDA/SDI34: J104.2, R103.1, U35.24
SDA/SDI35: J107.2, R106.1, U36.24
SDA/SDI36: J110.2, R109.1, U37.24
SDA/SDI37: J113.2, R112.1, U38.24
SDA/SDI38: J116.2, R115.1, U39.24
SDA/SDI39: J119.2, R118.1, U40.24
SDA/SDI40: J122.2, R121.1, U41.24
SDA/SDI41: J125.2, R124.1, U42.24
SDA/SDI42: J128.2, R127.1, U43.24
SDA/SDI43: J131.2, R130.1, U44.24
SDA/SDI44: J134.2, R133.1, U45.24
SDA/SDI45: J137.2, R136.1, U46.24
SDA/SDI46: J140.2, R139.1, U47.24
SDA/SDI47: J143.2, R142.1, U48.24
SDA/SDI48: J146.2, R145.1, U49.24
SDA/SDI49: J149.2, R148.1, U50.24
SDA/SDI50: J152.2, R151.1, U51.24
SDA/SDI51: J155.2, R154.1, U52.24
SDA/SDI52: J158.2, R157.1, U53.24
SDA/SDI53: J161.2, R160.1, U54.24
SDA/SDI54: J164.2, R163.1, U55.24
SDA/SDI55: J167.2, R166.1, U56.24
SDA/SDI56: J170.2, R169.1, U57.24
SDA/SDI57: J173.2, R172.1, U58.24
SDA/SDI58: J176.2, R175.1, U59.24
SDA/SDI59: J179.2, R178.1, U60.24
SDA/SDI60: J182.2, R181.1, U61.24
SDA/SDI61: J185.2, R184.1, U62.24
SDA/SDI62: J188.2, R187.1, U63.24
SDA/SDI63: J191.2, R190.1, U64.24
SDA/SDI64: J194.2, R193.1, U65.24
SDA/SDI65: J197.2, R196.1, U66.24
SDA/SDI66: J200.2, R199.1, U67.24
SDA/SDI67: J203.2, R202.1, U68.24
SDA/SDI68: J206.2, R205.1, U69.24
SDA/SDI69: J209.2, R208.1, U70.24
SDA/SDI70: J212.2, R211.1, U71.24
SDA/SDI71: J215.2, R214.1, U72.24
VDD: C2.1, J1.3, SJ1.1, U1.13
VDD1: C4.1, J5.3, SJ3.1, U2.13
VDD2: C6.1, J8.3, SJ5.1, U3.13
VDD3: C8.1, J11.3, SJ7.1, U4.13
VDD4: C10.1, J14.3, SJ9.1, U5.13
VDD5: C12.1, J17.3, SJ11.1, U6.13
VDD6: C14.1, J20.3, SJ13.1, U7.13
VDD7: C16.1, J23.3, SJ15.1, U8.13
VDD8: C18.1, J26.3, SJ17.1, U9.13
VDD9: C20.1, J29.3, SJ19.1, U10.13
VDD10: C22.1, J32.3, SJ21.1, U11.13
VDD11: C24.1, J35.3, SJ23.1, U12.13
VDD12: C26.1, J38.3, SJ25.1, U13.13
VDD13: C28.1, J41.3, SJ27.1, U14.13
VDD14: C30.1, J44.3, SJ29.1, U15.13
VDD15: C32.1, J47.3, SJ31.1, U16.13
VDD16: C34.1, J50.3, SJ33.1, U17.13
VDD17: C36.1, J53.3, SJ35.1, U18.13
VDD18: C38.1, J56.3, SJ37.1, U19.13
VDD19: C40.1, J59.3, SJ39.1, U20.13
VDD20: C42.1, J62.3, SJ41.1, U21.13
VDD21: C44.1, J65.3, SJ43.1, U22.13
VDD22: C46.1, J68.3, SJ45.1, U23.13
VDD23: C48.1, J71.3, SJ47.1, U24.13
VDD24: C50.1, J74.3, SJ49.1, U25.13
VDD25: C52.1, J77.3, SJ51.1, U26.13
VDD26: C54.1, J80.3, SJ53.1, U27.13
VDD27: C56.1, J83.3, SJ55.1, U28.13
VDD28: C58.1, J86.3, SJ57.1, U29.13
VDD29: C60.1, J89.3, SJ59.1, U30.13
VDD30: C62.1, J92.3, SJ61.1, U31.13
VDD31: C64.1, J95.3, SJ63.1, U32.13
VDD32: C66.1, J98.3, SJ65.1, U33.13
VDD33: C68.1, J101.3, SJ67.1, U34.13
VDD34: C70.1, J104.3, SJ69.1, U35.13
VDD35: C72.1, J107.3, SJ71.1, U36.13
VDD36: C74.1, J110.3, SJ73.1, U37.13
VDD37: C76.1, J113.3, SJ75.1, U38.13
VDD38: C78.1, J116.3, SJ77.1, U39.13
VDD39: C80.1, J119.3, SJ79.1, U40.13
VDD40: C82.1, J122.3, SJ81.1, U41.13
VDD41: C84.1, J125.3, SJ83.1, U42.13
VDD42: C86.1, J128.3, SJ85.1, U43.13
VDD43: C88.1, J131.3, SJ87.1, U44.13
VDD44: C90.1, J134.3, SJ89.1, U45.13
VDD45: C92.1, J137.3, SJ91.1, U46.13
VDD46: C94.1, J140.3, SJ93.1, U47.13
VDD47: C96.1, J143.3, SJ95.1, U48.13
VDD48: C98.1, J146.3, SJ97.1, U49.13
VDD49: C100.1, J149.3, SJ99.1, U50.13
VDD50: C102.1, J152.3, SJ101.1, U51.13
VDD51: C104.1, J155.3, SJ103.1, U52.13
VDD52: C106.1, J158.3, SJ105.1, U53.13
VDD53: C108.1, J161.3, SJ107.1, U54.13
VDD54: C110.1, J164.3, SJ109.1, U55.13
VDD55: C112.1, J167.3, SJ111.1, U56.13
VDD56: C114.1, J170.3, SJ113.1, U57.13
VDD57: C116.1, J173.3, SJ115.1, U58.13
VDD58: C118.1, J176.3, SJ117.1, U59.13
VDD59: C120.1, J179.3, SJ119.1, U60.13
VDD60: C122.1, J182.3, SJ121.1, U61.13
VDD61: C124.1, J185.3, SJ123.1, U62.13
VDD62: C126.1, J188.3, SJ125.1, U63.13
VDD63: C128.1, J191.3, SJ127.1, U64.13
VDD64: C130.1, J194.3, SJ129.1, U65.13
VDD65: C132.1, J197.3, SJ131.1, U66.13
VDD66: C134.1, J200.3, SJ133.1, U67.13
VDD67: C136.1, J203.3, SJ135.1, U68.13
VDD68: C138.1, J206.3, SJ137.1, U69.13
VDD69: C140.1, J209.3, SJ139.1, U70.13
VDD70: C142.1, J212.3, SJ141.1, U71.13
VDD71: C144.1, J215.3, SJ143.1, U72.13
VDDIO: J3.1, R1.2, R2.2, R3.2, SJ1.2, U1.1, U1.8
VDDIO1: J6.1, R4.2, R5.2, R6.2, SJ3.2, U2.1, U2.8
VDDIO2: J9.1, R7.2, R8.2, R9.2, SJ5.2, U3.1, U3.8
VDDIO3: J12.1, R10.2, R11.2, R12.2, SJ7.2, U4.1, U4.8
VDDIO4: J15.1, R13.2, R14.2, R15.2, SJ9.2, U5.1, U5.8
VDDIO5: J18.1, R16.2, R17.2, R18.2, SJ11.2, U6.1, U6.8
VDDIO6: J21.1, R19.2, R20.2, R21.2, SJ13.2, U7.1, U7.8
VDDIO7: J24.1, R22.2, R23.2, R24.2, SJ15.2, U8.1, U8.8
VDDIO8: J27.1, R25.2, R26.2, R27.2, SJ17.2, U9.1, U9.8
VDDIO9: J30.1, R28.2, R29.2, R30.2, SJ19.2, U10.1, U10.8
VDDIO10: J33.1, R31.2, R32.2, R33.2, SJ21.2, U11.1, U11.8
VDDIO11: J36.1, R34.2, R35.2, R36.2, SJ23.2, U12.1, U12.8
VDDIO12: J39.1, R37.2, R38.2, R39.2, SJ25.2, U13.1, U13.8
VDDIO13: J42.1, R40.2, R41.2, R42.2, SJ27.2, U14.1, U14.8
VDDIO14: J45.1, R43.2, R44.2, R45.2, SJ29.2, U15.1, U15.8
VDDIO15: J48.1, R46.2, R47.2, R48.2, SJ31.2, U16.1, U16.8
VDDIO16: J51.1, R49.2, R50.2, R51.2, SJ33.2, U17.1, U17.8
VDDIO17: J54.1, R52.2, R53.2, R54.2, SJ35.2, U18.1, U18.8
VDDIO18: J57.1, R55.2, R56.2, R57.2, SJ37.2, U19.1, U19.8
VDDIO19: J60.1, R58.2, R59.2, R60.2, SJ39.2, U20.1, U20.8
VDDIO20: J63.1, R61.2, R62.2, R63.2, SJ41.2, U21.1, U21.8
VDDIO21: J66.1, R64.2, R65.2, R66.2, SJ43.2, U22.1, U22.8
VDDIO22: J69.1, R67.2, R68.2, R69.2, SJ45.2, U23.1, U23.8
VDDIO23: J72.1, R70.2, R71.2, R72.2, SJ47.2, U24.1, U24.8
VDDIO24: J75.1, R73.2, R74.2, R75.2, SJ49.2, U25.1, U25.8
VDDIO25: J78.1, R76.2, R77.2, R78.2, SJ51.2, U26.1, U26.8
VDDIO26: J81.1, R79.2, R80.2, R81.2, SJ53.2, U27.1, U27.8
VDDIO27: J84.1, R82.2, R83.2, R84.2, SJ55.2, U28.1, U28.8
VDDIO28: J87.1, R85.2, R86.2, R87.2, SJ57.2, U29.1, U29.8
VDDIO29: J90.1, R88.2, R89.2, R90.2, SJ59.2, U30.1, U30.8
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
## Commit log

2015-11-02 Added axes
2015-11-02 Flipped x-axis on bottom
2015-11-02 Added v-score note
2015-11-02 Move dimensions to measures layer
2015-11-05 Loaded up new DRC
2015-11-06 Added mag axes
2015-11-09 Fixed silk and info
2016-01-04 Added stubs to NC pads on main IC and moved silk
2016-05-05 Tweaked some silk
2016-05-09 Removed bits of dimension on v-score
2016-06-01 Tweaked silk
2016-06-01 created panel v10
2016-07-19 Renamed to add branding
2016-07-27 Fixed up README.md
2016-07-27 Squashed 'Libraries/Arduino/' content from commit f25da84
    git-subtree-dir: Libraries/Arduino
    git-subtree-split: f25da84cb50444ab5acb54757738777533fbe2e1
2016-08-09 Fixed transposed chars in silk
2016-08-09 Removed exposed pad copper from PCB
2016-08-09 Incremented version number
2016-08-12 Repanel for silk revision
    Repaneled for silk revision
2017-01-03 adding SPI feature
2017-01-16 Fixed broken image link
    Image was changed.
2017-01-16 Fixed formatting
2017-01-16 Fixed broken link
2018-04-12 Updated axes of sensors in MahonyQuaternionUpdate function call.
2018-05-19 Added methods for setting sensor scales
2018-05-19 Made setting scales clearer to use
2018-09-25 Remove Arduino library subtree
2018-11-09 Add note on available Arduino libraries
